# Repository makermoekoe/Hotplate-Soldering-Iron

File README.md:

# Hotplate Soldering Iron

__For more informations to this project you can visit my website [makermoekoe.com](https://www.makermoekoe.com)__

(New version)

(Old version)

(Click on the images for a small video.)

Basic idea of the hotplate is slightly different from the standard tools like a reflow oven or soldering irons. The heat is supplied from the bottom of the PCB.

__What you will need:__

- an old iron
- microcontroller (I used a wemos d1 mini, but any will work)
- solid state relay 25A
- thermocouple sensor (a fast one...)
- 182x64 pixels oled display
- 5V DC power supply
- button, potentiometer and wires
- piece of wood and screws

Something similar is the Reflow Skillet from SparkFun: https://www.sparkfun.com/tutorials/59. They tested several methods to solder SMD components to PCBs and it turns out that their Skillet is the best solution for makers with a small budget. Inspired by this, my first thoughts about this old flatiron I found in the garage were to build a similar hot plate thing for soldering. And it turns out that this is working like a charm.

Concept of this is that the wemos d1 mini controls the solid state relay based on temperature informations from the thermocouple sensor, which I placed with some heat resistant kapton tape directly onto the iron (actually the sensor should be placed onto the PCB for preciser temperature readings). If you have a really fast iron than maybe you should use something like a PID controller. For me and my very sluggish iron a normal threshold based control is enough for now. I added my simple threshold code to this repository.

It takes about 3 minutes for the whole soldering process, which is very fast, compared to some professional solutions like reflow ovens. Maximal temperature is something about 220-240 degrees, depending on several things like used solder paste, PCB thickness, ...

__Conclusion:__

__Pro__
- works like a charm
- very low cost (I found all components at home)
- very fast soldering
- simple to build
- small frame size, suitable in every maker lab

__Cons__
- works only for one side of a PCB
- sluggish heat control of the iron (cool down takes several minutes). The PCB has to be removed after soldering process to cool down.

## Build your own

I have published two videos for creating the peace of wood used as base plate and for connecting the wires to the pcb. Just click on the images below to start the videos.

When connecting the 230V power supply to your board be careful not to switch some wires, like I did :D

The three terminals are labeled with __SSR__ for solid state relay, __DC5V__ for the Wemos power supply and __Thermo__ for the thermocouple sensor. When switching the thermocouple sensor wires, the temperature on the display will get smaller when the plate gets hot. If this is the case, simply switch the __Thermo__ wires.

## Schematics

For the PCB I desoldered the MAX6675 thermocouple IC from the small breakout board and used it directly onto the PCB to safe a little bit of space. All other components are just connected via pin headers to the PCB. The 5V power supply, the thermocouple and the solid state relay on GPIO 8 are connected via those screw terminals.

<div>

</div>

## Printed Circuit Board

(Click on the image for a small video.)

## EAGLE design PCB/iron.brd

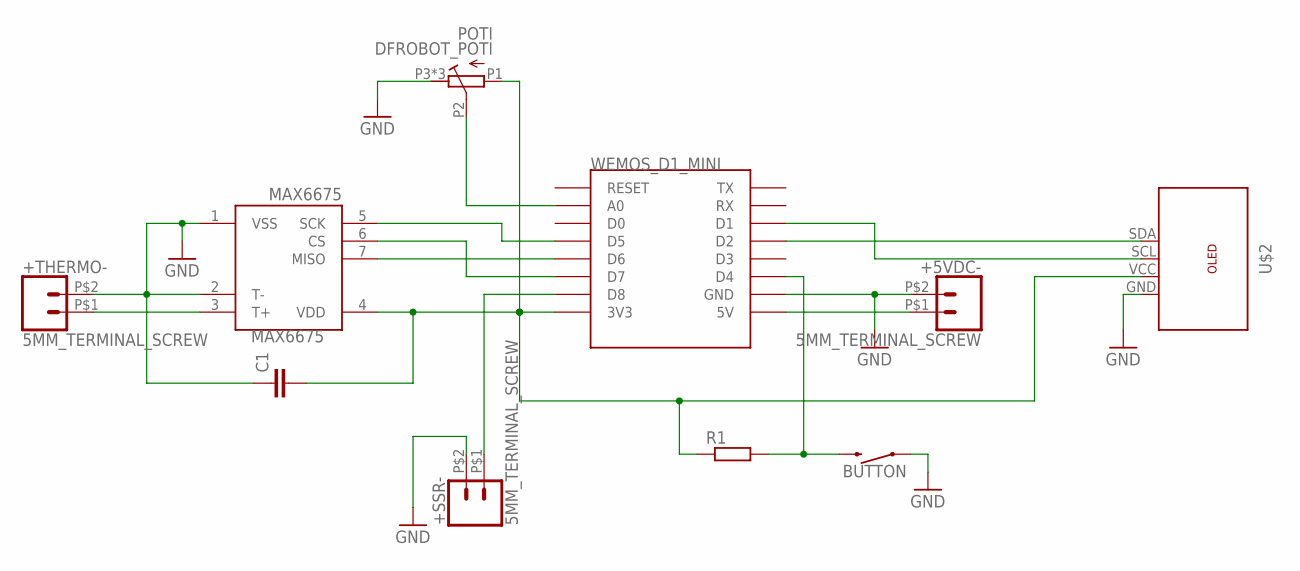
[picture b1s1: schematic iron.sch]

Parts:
+5VDC-: 5MM_TERMINAL_SCREW
+SSR-: 5MM_TERMINAL_SCREW
+THERMO-: 5MM_TERMINAL_SCREW
BUTTON: MOMENTARY-SWITCH-SPST-PTH-12MM; TACTILE_SWITCH_PTH_12MM
C1: C-EUC0603; C0603
MAX6675: MAX6675; SO08
POTI: DFROBOT_POTI
R1: R-EU_R0603; R0603
U$2: OLED128X64; OLED_128X64
WEMOS_D1_MINI: WEMOS-D1-MINI

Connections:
GND: +5VDC-.P$2 (2), +SSR-.P$2 (2), +THERMO-.P$2 (2), BUTTON.1, C1.1, MAX6675.1 (VSS), MAX6675.2 (T-), POTI.P3 (E), POTI.PG1 (E), POTI.PG2 (E), U$2.GND, WEMOS_D1_MINI.GND
unnamed: MAX6675.5 (SCK), WEMOS_D1_MINI.D5
unnamed: MAX6675.6 (CS), WEMOS_D1_MINI.D7
unnamed: MAX6675.7 (MISO), WEMOS_D1_MINI.D6
unnamed: C1.2, MAX6675.4 (VDD), POTI.P1 (A), R1.1, U$2.VCC, WEMOS_D1_MINI.3V3
unnamed: U$2.SCL, WEMOS_D1_MINI.D1
unnamed: U$2.SDA, WEMOS_D1_MINI.D2
unnamed: +SSR-.P$1 (1), WEMOS_D1_MINI.D8
unnamed: +THERMO-.P$1 (1), MAX6675.3 (T+)
unnamed: +5VDC-.P$1 (1), WEMOS_D1_MINI.5V
unnamed: BUTTON.3 (2), R1.2, WEMOS_D1_MINI.D4
unnamed: POTI.P2 (S), WEMOS_D1_MINI.A0

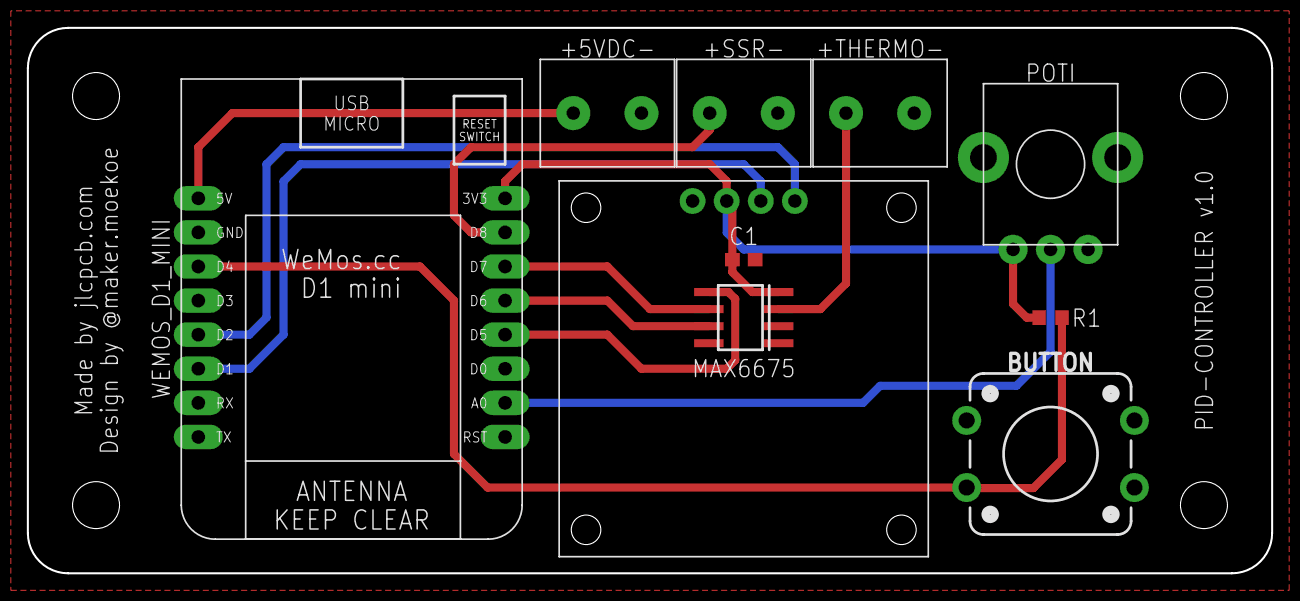
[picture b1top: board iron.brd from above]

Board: 2 copper layers, 92.7 x 40.6 mm, 10 parts (0 on the bottom side), 12 nets.

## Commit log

2019-04-19 initial
2019-04-22 added PCB
2019-04-22 added video
2019-05-22 added version 2
2019-05-22 added code version 2
2019-05-22 version 2
2019-09-13 shifted makermoekoe.net
2019-09-13 redirect website
2020-02-05 added gerber
2020-02-05 updated makermoekoe link

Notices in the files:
parts and their libraries:
SparkFun-Switches: Licensing: Creative Commons ShareAlike 4.0 International - https://creativecommons.org/licenses/by-sa/4.0
